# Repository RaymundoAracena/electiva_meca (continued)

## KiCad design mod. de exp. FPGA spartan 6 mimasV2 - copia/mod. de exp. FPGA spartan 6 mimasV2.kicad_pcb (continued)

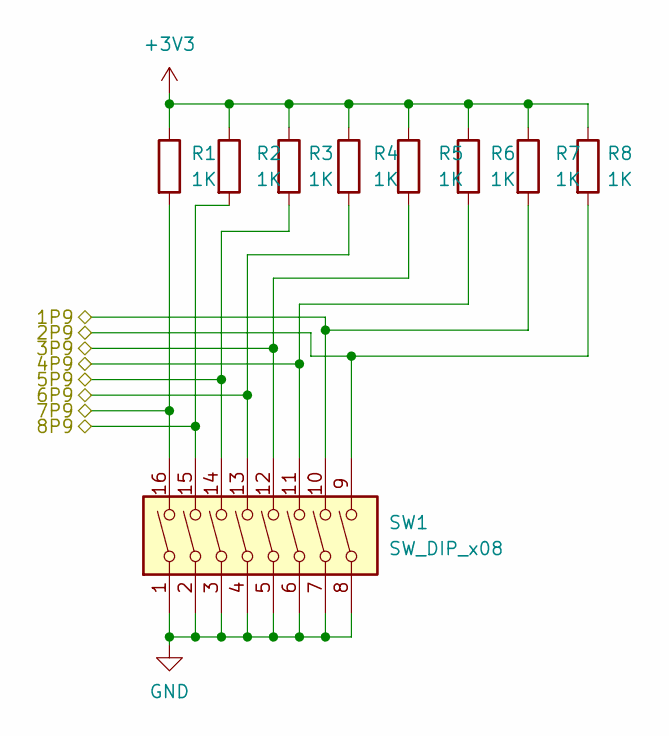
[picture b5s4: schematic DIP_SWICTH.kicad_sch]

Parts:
R1, R2, R3, R4, R5, R6, R7, R8: 1K; R_Axial_DIN0207_L6.3mm_D2.5mm_P10.16mm_Horizontal
SW1: SW_DIP_x08; SW_DIP_SPSTx08_Slide_6.7x21.88mm_W7.62mm_P2.54mm_LowProfile

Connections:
/DIP_SWITCH/1P9: R8.2, SW1.9; also elsewhere on the board
/DIP_SWITCH/2P9: R7.2, SW1.10; also elsewhere on the board
/DIP_SWITCH/3P9: R6.2, SW1.11; also elsewhere on the board
/DIP_SWITCH/4P9: R5.2, SW1.12; also elsewhere on the board
/DIP_SWITCH/5P9: R4.2, SW1.13; also elsewhere on the board
/DIP_SWITCH/6P9: R3.2, SW1.14; also elsewhere on the board
/DIP_SWITCH/7P9: R2.2, SW1.15; also elsewhere on the board
/DIP_SWITCH/8P9: R1.2, SW1.16; also elsewhere on the board

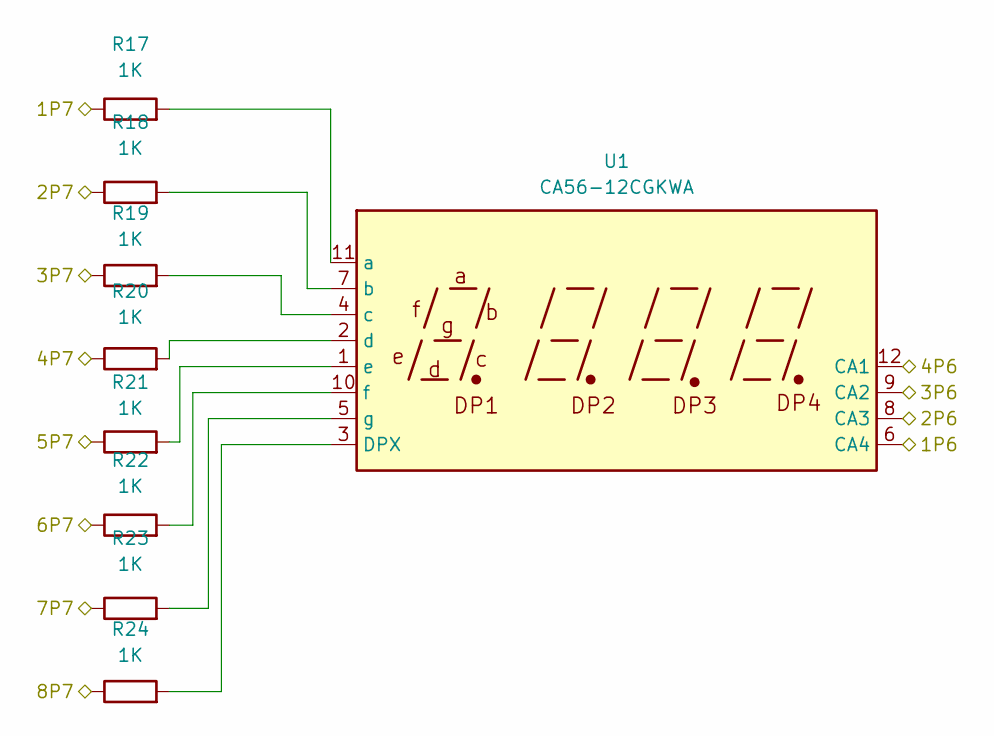
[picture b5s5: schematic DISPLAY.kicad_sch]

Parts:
R17, R18, R19, R20, R21, R22, R23, R24: 1K; R_Axial_DIN0207_L6.3mm_D2.5mm_P7.62mm_Horizontal
U1: CA56-12CGKWA

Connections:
/DISPLAY/1P6: U1.6 (CA4); also elsewhere on the board
/DISPLAY/1P7: R17.1; also elsewhere on the board
/DISPLAY/2P6: U1.8 (CA3); also elsewhere on the board
/DISPLAY/2P7: R18.1; also elsewhere on the board
/DISPLAY/3P6: U1.9 (CA2); also elsewhere on the board
/DISPLAY/3P7: R19.1; also elsewhere on the board
/DISPLAY/4P6: U1.12 (CA1); also elsewhere on the board
/DISPLAY/4P7: R20.1; also elsewhere on the board
/DISPLAY/5P7: R21.1; also elsewhere on the board
/DISPLAY/6P7: R22.1; also elsewhere on the board
/DISPLAY/7P7: R23.1; also elsewhere on the board
/DISPLAY/8P7: R24.1; also elsewhere on the board
unnamed: R24.2, U1.3 (DPX)
unnamed: R17.2, U1.11 (a)
unnamed: R18.2, U1.7 (b)
unnamed: R19.2, U1.4 (c)
unnamed: R20.2, U1.2 (d)
unnamed: R21.2, U1.1 (e)
unnamed: R22.2, U1.10 (f)
unnamed: R23.2, U1.5 (g)

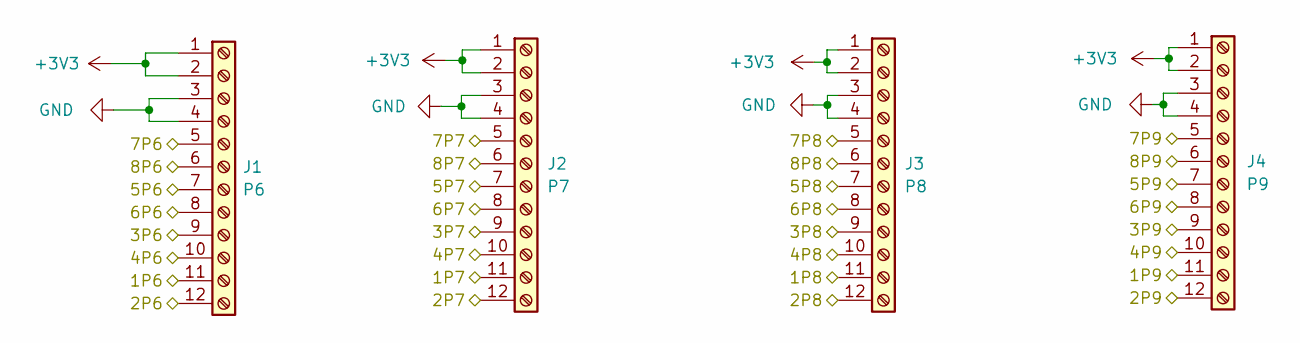
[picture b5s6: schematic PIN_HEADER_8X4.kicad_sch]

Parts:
J1: P6; PinHeader_2x06_P2.54mm_Horizontal
J2: P7; PinHeader_2x06_P2.54mm_Horizontal
J3: P8; PinHeader_2x06_P2.54mm_Horizontal
J4: P9; PinHeader_2x06_P2.54mm_Horizontal

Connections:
/DIP_SWITCH/1P9: J4.11; also elsewhere on the board
/DIP_SWITCH/2P9: J4.12; also elsewhere on the board
/DIP_SWITCH/3P9: J4.9; also elsewhere on the board
/DIP_SWITCH/4P9: J4.10; also elsewhere on the board
/DIP_SWITCH/5P9: J4.7; also elsewhere on the board
/DIP_SWITCH/6P9: J4.8; also elsewhere on the board
/DIP_SWITCH/7P9: J4.5; also elsewhere on the board
/DIP_SWITCH/8P9: J4.6; also elsewhere on the board
/DISPLAY/1P6: J1.11; also elsewhere on the board
/DISPLAY/1P7: J2.11; also elsewhere on the board
/DISPLAY/2P6: J1.12; also elsewhere on the board
/DISPLAY/2P7: J2.12; also elsewhere on the board
/DISPLAY/3P6: J1.9; also elsewhere on the board
/DISPLAY/3P7: J2.9; also elsewhere on the board
/DISPLAY/4P6: J1.10; also elsewhere on the board
/DISPLAY/4P7: J2.10; also elsewhere on the board
/DISPLAY/5P7: J2.7; also elsewhere on the board
/DISPLAY/6P7: J2.8; also elsewhere on the board
/DISPLAY/7P7: J2.5; also elsewhere on the board
/DISPLAY/8P7: J2.6; also elsewhere on the board
/LEDs/1P8: J3.11; also elsewhere on the board
/LEDs/2P8: J3.12; also elsewhere on the board
/LEDs/3P8: J3.9; also elsewhere on the board
/LEDs/4P8: J3.10; also elsewhere on the board
/LEDs/5P8: J3.7; also elsewhere on the board
/LEDs/6P8: J3.8; also elsewhere on the board
/LEDs/7P8: J3.5; also elsewhere on the board
/LEDs/8P8: J3.6; also elsewhere on the board
/PIN_HEADER_8X4/5P6: J1.7; also elsewhere on the board
/PIN_HEADER_8X4/6P6: J1.8; also elsewhere on the board
/PIN_HEADER_8X4/7P6: J1.5; also elsewhere on the board
/PIN_HEADER_8X4/8P6: J1.6; also elsewhere on the board

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
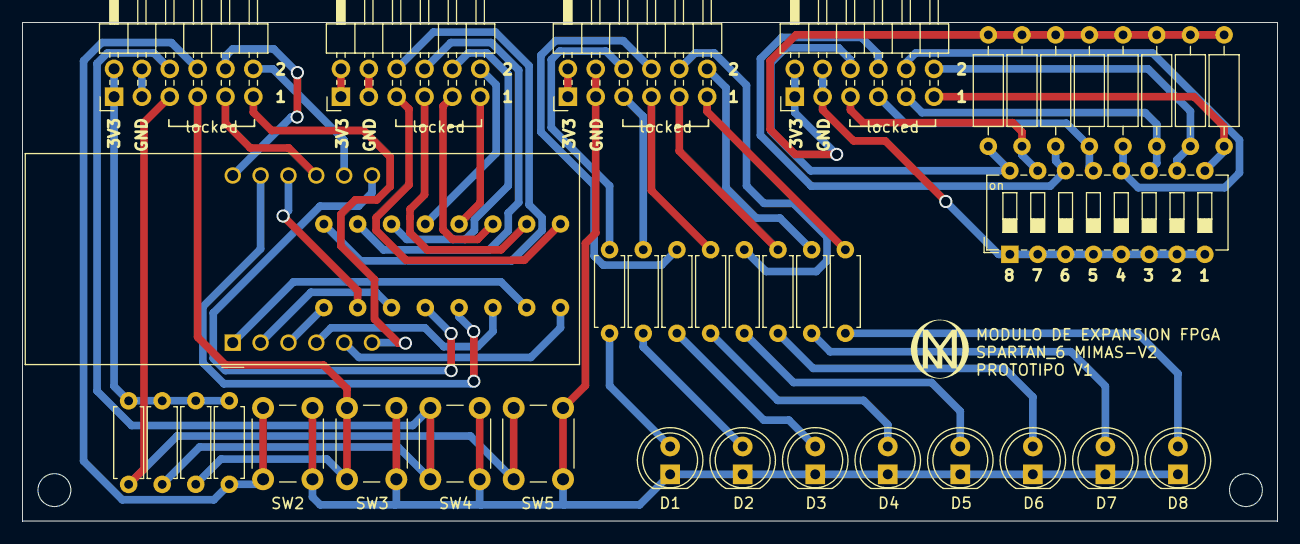
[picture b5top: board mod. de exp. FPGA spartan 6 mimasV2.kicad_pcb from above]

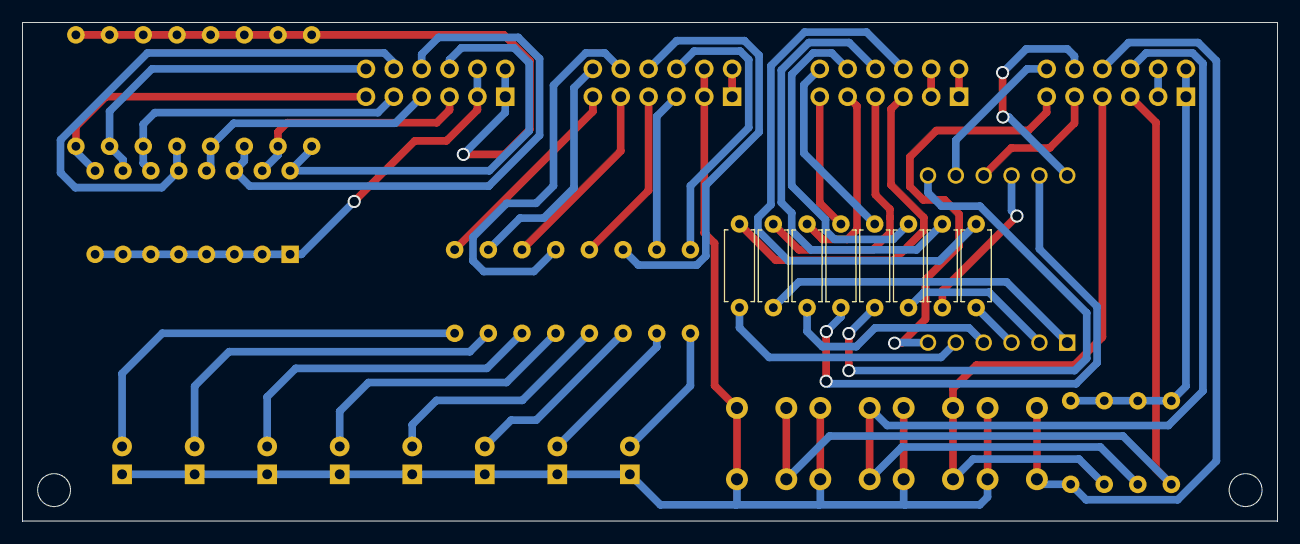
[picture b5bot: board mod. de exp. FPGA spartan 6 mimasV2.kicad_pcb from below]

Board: 2 copper layers, 114.4 x 45.5 mm, 46 parts (8 on the bottom side), 56 nets.

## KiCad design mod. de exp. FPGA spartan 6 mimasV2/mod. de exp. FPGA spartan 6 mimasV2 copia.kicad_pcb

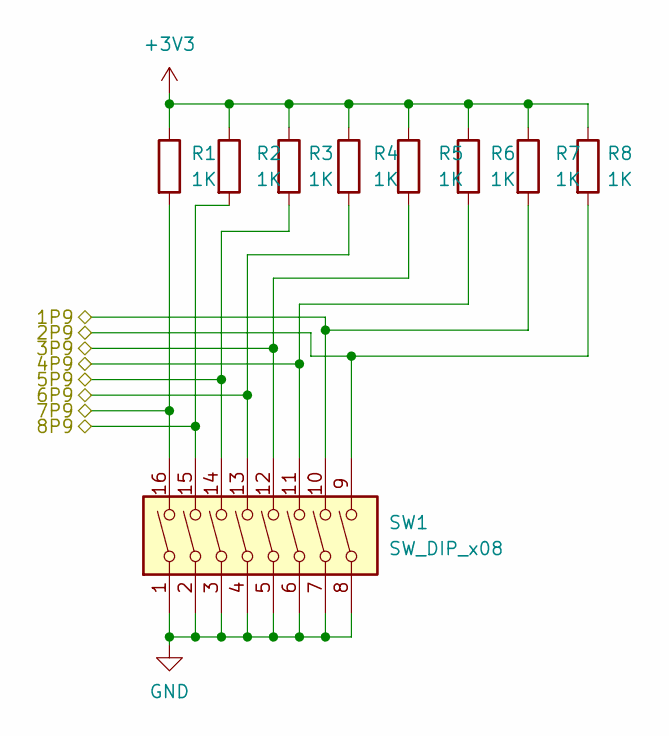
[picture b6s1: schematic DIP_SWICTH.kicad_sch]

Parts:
R1, R2, R3, R4, R5, R6, R7, R8: 1K; R_0805_2012Metric
SW1: SW_DIP_x08; SW_DIP_SPSTx08_Slide_6.7x21.88mm_W7.62mm_P2.54mm_LowProfile

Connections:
+3V3: R1.1, R2.1, R3.1, R4.1, R5.1, R6.1, R7.1, R8.1; also elsewhere on the board
/DIP_SWITCH/1P9: R7.2, SW1.10; also elsewhere on the board
/DIP_SWITCH/2P9: R8.2, SW1.9; also elsewhere on the board
/DIP_SWITCH/3P9: R5.2, SW1.12; also elsewhere on the board
/DIP_SWITCH/4P9: R6.2, SW1.11; also elsewhere on the board
/DIP_SWITCH/5P9: R3.2, SW1.14; also elsewhere on the board
/DIP_SWITCH/6P9: R4.2, SW1.13; also elsewhere on the board
/DIP_SWITCH/7P9: R1.2, SW1.16; also elsewhere on the board
/DIP_SWITCH/8P9: R2.2, SW1.15; also elsewhere on the board
GND: SW1.1, SW1.2, SW1.3, SW1.4, SW1.5, SW1.6, SW1.7, SW1.8; also elsewhere on the board

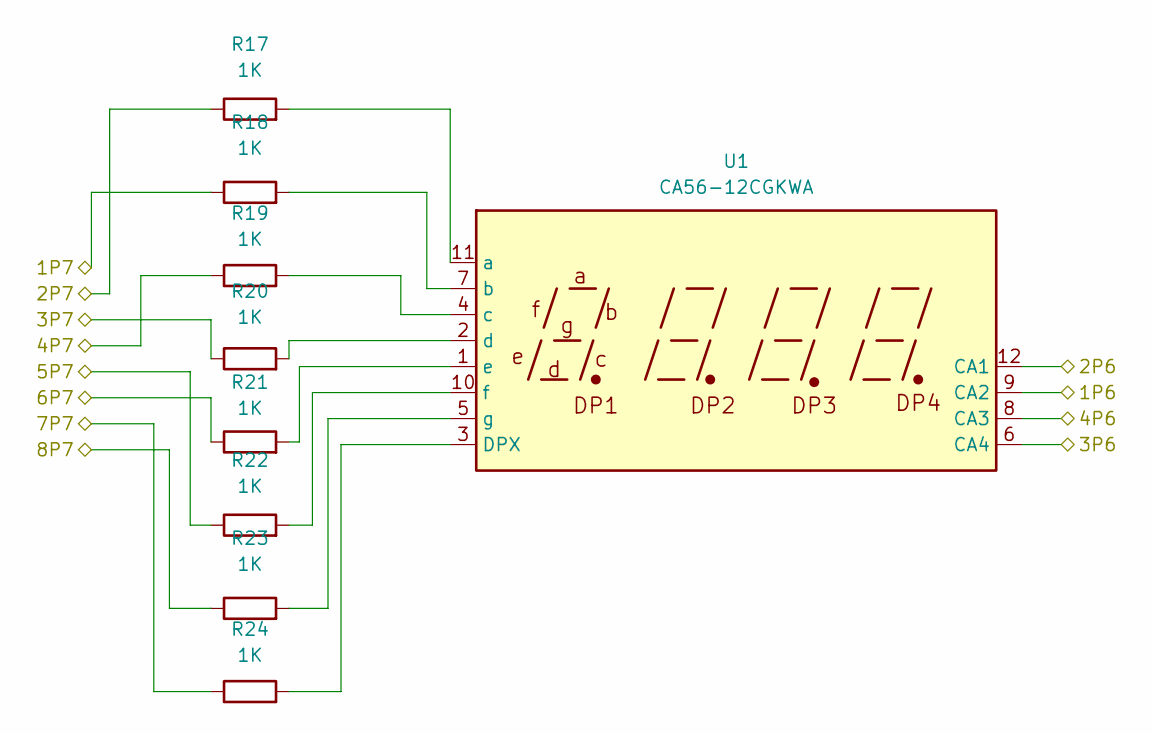
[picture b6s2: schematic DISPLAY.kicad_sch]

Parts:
R17, R18, R19, R20, R21, R22, R23, R24: 1K; R_0805_2012Metric
U1: CA56-12CGKWA

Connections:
/DISPLAY/1P6: U1.9 (CA2); also elsewhere on the board
/DISPLAY/1P7: R18.1; also elsewhere on the board
/DISPLAY/2P6: U1.12 (CA1); also elsewhere on the board
/DISPLAY/2P7: R17.1; also elsewhere on the board
/DISPLAY/3P6: U1.6 (CA4); also elsewhere on the board
/DISPLAY/3P7: R20.1; also elsewhere on the board
/DISPLAY/4P6: U1.8 (CA3); also elsewhere on the board
/DISPLAY/4P7: R19.1; also elsewhere on the board
/DISPLAY/5P7: R22.1; also elsewhere on the board
/DISPLAY/6P7: R21.1; also elsewhere on the board
/DISPLAY/7P7: R24.1; also elsewhere on the board
/DISPLAY/8P7: R23.1; also elsewhere on the board
unnamed: R17.2, U1.11 (a)
unnamed: R18.2, U1.7 (b)
unnamed: R19.2, U1.4 (c)
unnamed: R20.2, U1.2 (d)
unnamed: R21.2, U1.1 (e)
unnamed: R22.2, U1.10 (f)
unnamed: R23.2, U1.5 (g)
unnamed: R24.2, U1.3 (DPX)

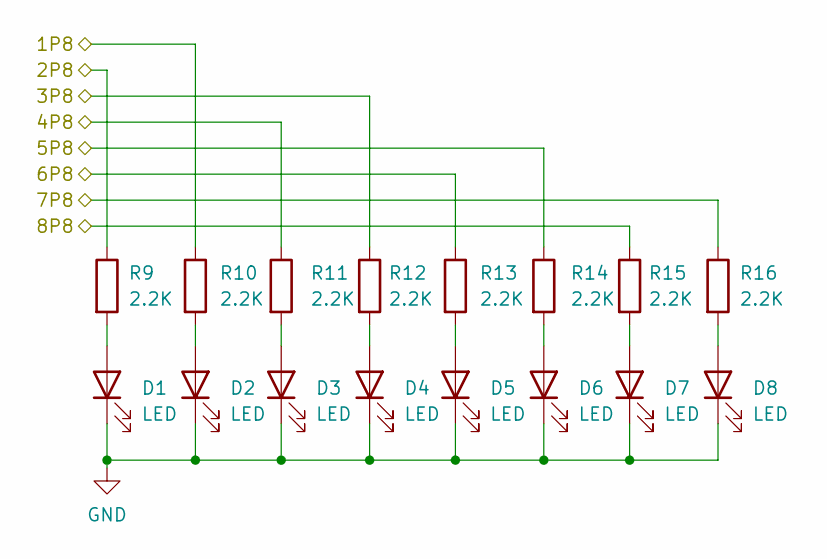
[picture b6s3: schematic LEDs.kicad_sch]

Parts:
D1, D2, D3, D4, D5, D6, D7, D8: LED; LED_0805_2012Metric
R9, R10, R11, R12, R13, R14, R15, R16: 2.2K; R_0805_2012Metric

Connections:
/LEDs/1P8: R10.1; also elsewhere on the board
/LEDs/2P8: R9.1; also elsewhere on the board
/LEDs/3P8: R12.1; also elsewhere on the board
/LEDs/4P8: R11.1; also elsewhere on the board
/LEDs/5P8: R14.1; also elsewhere on the board
/LEDs/6P8: R13.1; also elsewhere on the board
/LEDs/7P8: R16.1; also elsewhere on the board
/LEDs/8P8: R15.1; also elsewhere on the board
GND: D1.1 (K), D2.1 (K), D3.1 (K), D4.1 (K), D5.1 (K), D6.1 (K), D7.1 (K), D8.1 (K); also elsewhere on the board
unnamed: D1.2 (A), R9.2
unnamed: D2.2 (A), R10.2
unnamed: D3.2 (A), R11.2
unnamed: D4.2 (A), R12.2
unnamed: D5.2 (A), R13.2
unnamed: D6.2 (A), R14.2
unnamed: D7.2 (A), R15.2
unnamed: D8.2 (A), R16.2

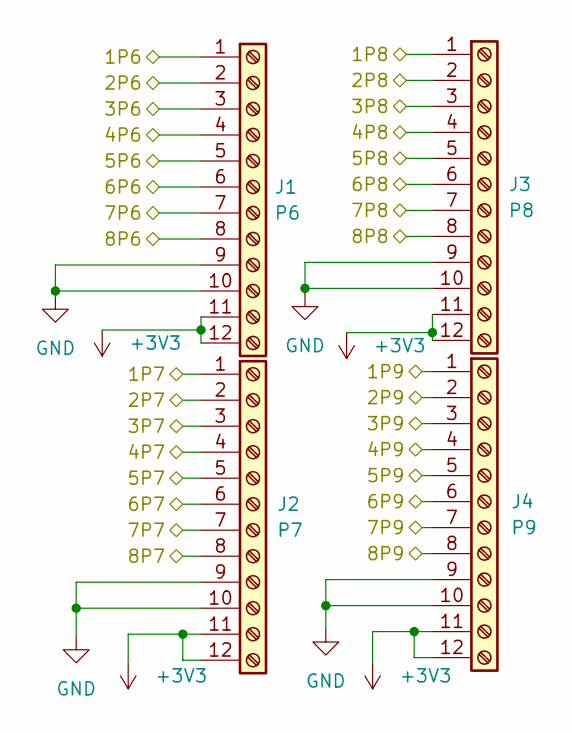
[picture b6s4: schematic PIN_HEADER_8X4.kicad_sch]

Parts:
J1: P6; PinHeader_2x06_P2.54mm_Vertical
J2: P7; PinHeader_2x06_P2.54mm_Vertical
J3: P8; PinHeader_2x06_P2.54mm_Vertical
J4: P9; PinHeader_2x06_P2.54mm_Vertical

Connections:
+3V3: J1.11, J1.12, J2.11, J2.12, J3.11, J3.12, J4.11, J4.12; also elsewhere on the board
/DIP_SWITCH/1P9: J4.1; also elsewhere on the board
/DIP_SWITCH/2P9: J4.2; also elsewhere on the board
/DIP_SWITCH/3P9: J4.3; also elsewhere on the board
/DIP_SWITCH/4P9: J4.4; also elsewhere on the board
/DIP_SWITCH/5P9: J4.5; also elsewhere on the board
/DIP_SWITCH/6P9: J4.6; also elsewhere on the board
/DIP_SWITCH/7P9: J4.7; also elsewhere on the board
/DIP_SWITCH/8P9: J4.8; also elsewhere on the board
/DISPLAY/1P6: J1.1; also elsewhere on the board
/DISPLAY/1P7: J2.1; also elsewhere on the board
/DISPLAY/2P6: J1.2; also elsewhere on the board
/DISPLAY/2P7: J2.2; also elsewhere on the board
/DISPLAY/3P6: J1.3; also elsewhere on the board
/DISPLAY/3P7: J2.3; also elsewhere on the board
/DISPLAY/4P6: J1.4; also elsewhere on the board
/DISPLAY/4P7: J2.4; also elsewhere on the board
/DISPLAY/5P7: J2.5; also elsewhere on the board
/DISPLAY/6P7: J2.6; also elsewhere on the board
/DISPLAY/7P7: J2.7; also elsewhere on the board
/DISPLAY/8P7: J2.8; also elsewhere on the board
/LEDs/1P8: J3.1; also elsewhere on the board
/LEDs/2P8: J3.2; also elsewhere on the board
/LEDs/3P8: J3.3; also elsewhere on the board
/LEDs/4P8: J3.4; also elsewhere on the board
/LEDs/5P8: J3.5; also elsewhere on the board
/LEDs/6P8: J3.6; also elsewhere on the board
/LEDs/7P8: J3.7; also elsewhere on the board
/LEDs/8P8: J3.8; also elsewhere on the board
/PIN_HEADER_8X4/5P6: J1.5; also elsewhere on the board
/PIN_HEADER_8X4/6P6: J1.6; also elsewhere on the board
/PIN_HEADER_8X4/7P6: J1.7; also elsewhere on the board
/PIN_HEADER_8X4/8P6: J1.8; also elsewhere on the board
GND: J1.9, J1.10, J2.9, J2.10, J3.9, J3.10, J4.9, J4.10; also elsewhere on the board

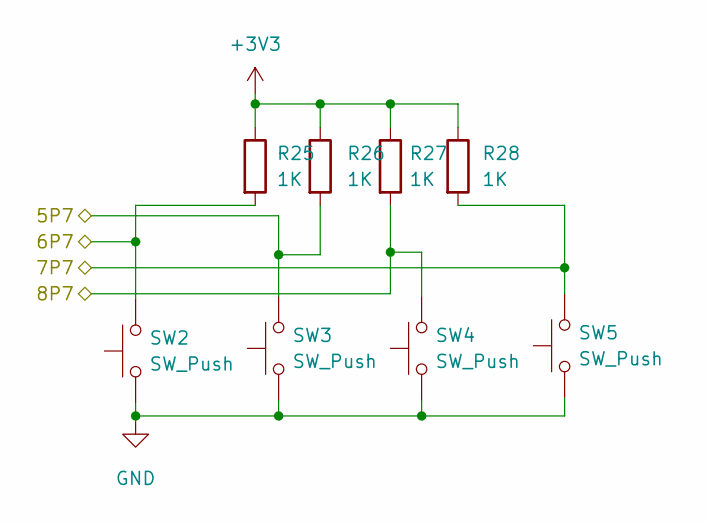
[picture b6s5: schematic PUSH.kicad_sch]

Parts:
R25, R26, R27, R28: 1K; R_0805_2012Metric
SW2, SW3, SW4, SW5: SW_Push; SW_PUSH_6mm

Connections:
+3V3: R25.1, R26.1, R27.1, R28.1; also elsewhere on the board
/PIN_HEADER_8X4/5P6: R26.2, SW3.2; also elsewhere on the board
/PIN_HEADER_8X4/6P6: R25.2, SW2.2; also elsewhere on the board
/PIN_HEADER_8X4/7P6: R28.2, SW5.2; also elsewhere on the board
/PIN_HEADER_8X4/8P6: R27.2, SW4.2; also elsewhere on the board
GND: SW2.1, SW3.1, SW4.1, SW5.1; also elsewhere on the board

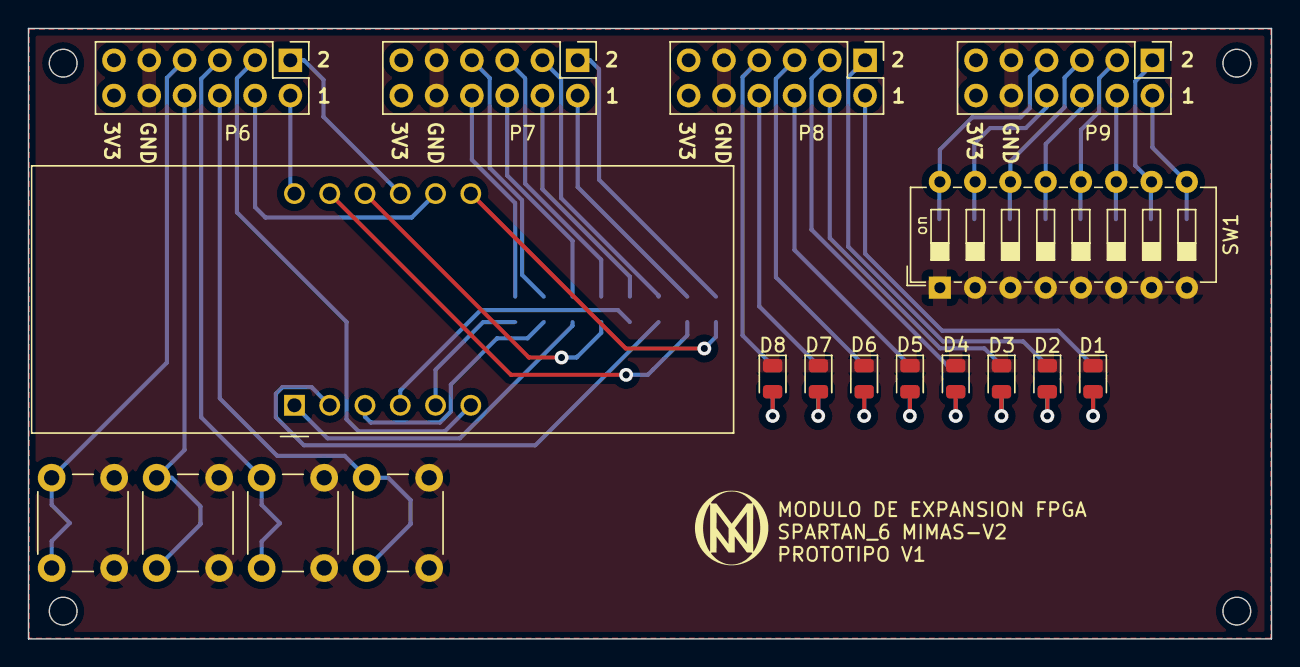
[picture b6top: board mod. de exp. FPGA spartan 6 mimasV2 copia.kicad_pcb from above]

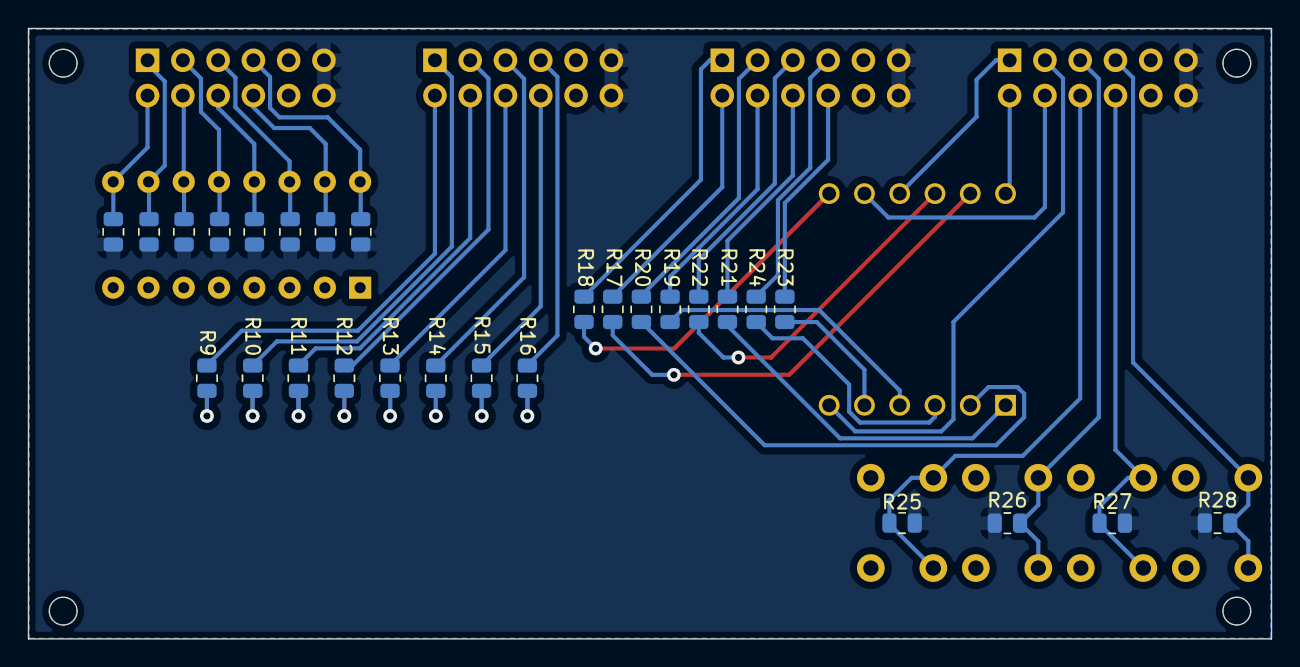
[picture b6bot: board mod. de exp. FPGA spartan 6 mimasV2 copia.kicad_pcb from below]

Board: 2 copper layers, 89.5 x 44.0 mm, 46 parts (28 on the bottom side), 50 nets.

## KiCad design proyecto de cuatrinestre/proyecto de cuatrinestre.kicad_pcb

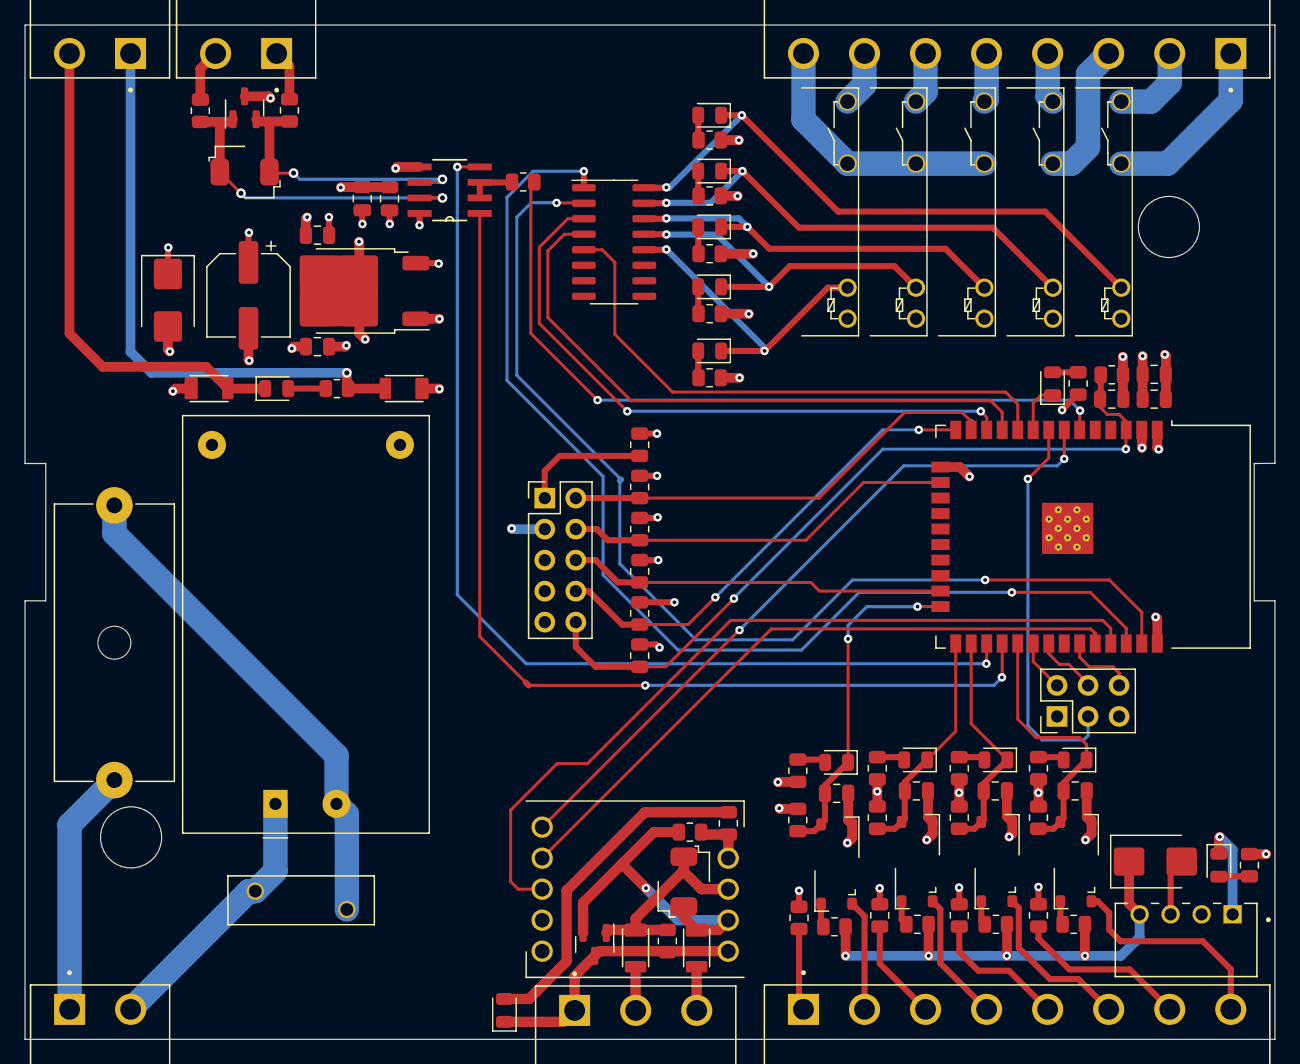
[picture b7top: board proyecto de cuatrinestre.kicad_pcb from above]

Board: 4 copper layers, 102.4 x 83.1 mm, 98 parts (0 on the bottom side), 85 nets.

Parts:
C1, C2, C3, C4, C5, C13: 0.1uF; C_0805_2012Metric
C7, C9, C10: 0.1uF / 25V; C_0805_2012Metric
C8: 0.1uF / 50V; C_0805_2012Metric
C11: 47uF; CP_Elec_6.3x5.7
C12: 22uF; C_0805_2012Metric
D1, D2, D3, D4, D5, D6, D7, D8, D9, D10, D12, D14, D16: LED; LED_0805_2012Metric
D11, D13: SM712_SOT23; SOT-23
D17, D18: 1SMA5918BT3G; D_SMB
F1, F2: PTS120660V010; RESC3115X65N
F3: Fuse; Fuseholder_Cylinder-5x20mm_Schurter_0031_8201_Horizontal_Op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
F4, F5: Fuse; RESC3115X65N
J1, J2, J3: Screw_Terminal_01x02; CUI_TBP04R12-500-02GR
J4: Screw_Terminal_01x03; CUI_TBP04R12-500-03GR
J5, J6: Screw_Terminal_01x08; CUI_TBP04R12-500-08GR
J7: Screw_Terminal_01x06; PinHeader_2x03_P2.54mm_Vertical
J8: ESP32-JTAG; PinHeader_2x05_P2.54mm_Vertical
PS1: HLK-PM12; Converter_ACDC_HiLink_HLK-PMxx
R1, R3, R9, R11: 330; R_0805_2012Metric
R2, R4, R10, R12, R43, R44: 10; R_0805_2012Metric
R5, R6, R13, R14: 10k; R_0805_2012Metric
R7, R8, R15, R16, R39: 470; R_0805_2012Metric
R17, R18, R19, R20, R21: 1K; R_0805_2012Metric
R22: 2.2k; R_0805_2012Metric
R23, R24: 2.2; R_0805_2012Metric
R27, R33: 22K; R_0805_2012Metric
R28, R29, R30, R31, R32: 10K; R_0805_2012Metric
R42: 10 / 1%; R_0805_2012Metric
R45, R47: R; R_0805_2012Metric
RV1: V10E275P; VAR_B72210S1140K501
U1: TD521D485H-E
U2, U3, U4, U5: FODM2705
U6: ULN2003A; SOIC-16_3.9x9.9mm_P1.27mm
U7, U8, U9, U10, U11: AZ921
U12, U14: SMBJ12CA
U13: SP485ECN-L; SOIC127P600X175-8N
U15: 3v3 NJM2885DL1-33; TO-252-2
U16: B0303S-W2R2; CONV_B0505S-1WR2
U17: ESP32-WROOM-32

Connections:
+3V3: D18.1, R1.1, R3.1, R9.1, R11.1, U16.4 (OUT+)
+12V: C9.1, F4.1, PS1.4 (+Vout), R17.2, R18.2, R19.2, R20.2, R21.2, U7.1, U8.1, U9.1, U10.1, U11.1, U15.1 (Vin)
/ROOMLINK/CON-A-: F2.2, J4.3
/ROOMLINK/CON-B+: F1.2, J4.2
/ROOMLINK/CON-DC+: F4.2, J2.1, R45.1
/ROOMLINK/CON-DC-: D14.1 (K), F5.2, J2.2
/ROOMLINK/CON-FAN1: J5.7, U9.4
/ROOMLINK/CON-FAN2: J5.6, U10.4
/ROOMLINK/CON-FAN3: J5.5, U11.4
/ROOMLINK/CON-FAN-C: J5.8, U9.3, U10.3, U11.3
/ROOMLINK/CON-IN1+: J6.8, U2.2
/ROOMLINK/CON-IN1-: J6.7, R2.2
/ROOMLINK/CON-IN2+: J6.6, U3.2
/ROOMLINK/CON-IN2-: J6.5, R4.2
/ROOMLINK/CON-IN3+: J6.4, U5.2
/ROOMLINK/CON-IN3-: J6.3, R12.2
/ROOMLINK/CON-IN4+: J6.2, U4.2
/ROOMLINK/CON-IN4-: J6.1, R10.2
/ROOMLINK/CON-L1: F3.2, J1.1
/ROOMLINK/CON-LCDA-: J3.1, R43.2
/ROOMLINK/CON-LCDB+: J3.2, R44.2
/ROOMLINK/CON-NEUT: J1.2, PS1.1 (AC/L), RV1.1
/ROOMLINK/CON-OUT1A: J5.3, U7.3
/ROOMLINK/CON-OUT1B: J5.4, U7.4
/ROOMLINK/CON-OUT2A: J5.1, U8.3
/ROOMLINK/CON-OUT2B: J5.2, U8.4
/ROOMLINK/CONTROL/COM_RS485_LCD: R42.1, U17.6 (IO34)
/ROOMLINK/CONTROL/CON_RS485_eXT: U1.5 (CON), U17.7 (IO35)
/ROOMLINK/CONTROL/INPUT_1_MICRO: C1.1, D1.1 (K), R5.2, U2.4, U17.29 (IO5)
/ROOMLINK/CONTROL/INPUT_2_MICRO: C2.1, D2.1 (K), R6.2, U3.4, U17.26 (IO4)
/ROOMLINK/CONTROL/INPUT_3_MICRO: C4.1, D4.1 (K), R14.2, U5.4, U17.25 (IO0)
/ROOMLINK/CONTROL/INPUT_4_MICRO: C3.1, D3.1 (K), R13.2, U4.4, U17.24 (IO2)
/ROOMLINK/CONTROL/RLY_FAN1_MICRO: U6.5 (I5), U17.10 (IO25)
/ROOMLINK/CONTROL/RLY_FAN2_MICRO: U6.4 (I4), U17.11 (IO26)
/ROOMLINK/CONTROL/RLY_FAN3_MICRO: U6.3 (I3), U17.12 (IO27)
/ROOMLINK/CONTROL/RLY_OUT1_MICRO: U6.1 (I1), U17.36 (IO22)
/ROOMLINK/CONTROL/RLY_OUT2_MICRO: U6.2 (I2), U17.37 (IO23)
/ROOMLINK/CONTROL/Rx_RS485_eXT: U1.4 (RXD), U17.34 (RXD0/IO3)
/ROOMLINK/CONTROL/Rx_RS485_lcd: U13.4 (DI), U17.27 (IO16)
/ROOMLINK/CONTROL/Tx_RS485_LCD: U13.1 (RO), U17.28 (IO17)
/ROOMLINK/CONTROL/Tx_RS485_eXT: U1.3 (TXD), U17.35 (TXD0/IO1)
/ROOMLINK/RGND: D10.1 (K), D11.3 (common), J4.1, R23.1, U1.10 (RGND)
GND: C1.2, C2.2, C3.2, C4.2, C7.2, C8.2, C9.2, C10.2, C11.2, C12.2, C13.2, D13.3 (common), D16.1 (K), D17.2, F5.1, J7.5, J8.3 (GND), J8.9 (GNDDetect), PS1.3 (-Vout), U1.2 (GND), U2.3, U3.3, U4.3, U5.3, U13.5 (GND), U15.2 (GND), U16.1 (IN-), U17.1 (GND), U17.15 (GND), U17.38 (GND), U17.39 (GND)
GNDA: D18.2, R2.1, R4.1, R10.1, R12.1, U16.3 (OUT-)
unnamed: D1.2 (A), R7.2
unnamed: D2.2 (A), R8.2
unnamed: D3.2 (A), R15.2
unnamed: D4.2 (A), R16.2
unnamed: D5.2 (A), R17.1
unnamed: D5.1 (K), U6.16 (O1), U8.2
unnamed: D6.2 (A), R18.1
unnamed: D6.1 (K), U6.15 (O2), U7.2
unnamed: D7.2 (A), R19.1
unnamed: D7.1 (K), U6.14 (O3), U11.2
unnamed: D8.2 (A), R20.1
unnamed: D8.1 (K), U6.13 (O4), U10.2
unnamed: D9.2 (A), R21.1
unnamed: D9.1 (K), U6.12 (O5), U9.2
unnamed: D10.2 (A), R24.2
unnamed: D11.1 (A1), F1.1, R23.2, U1.8 (B), U12.1
unnamed: D11.2 (A2), F2.1, R22.2, U1.9 (A), U12.2
unnamed: D12.2 (A), R39.1
unnamed: D12.1 (K), U17.9 (IO33)
unnamed: D13.1 (A1), R44.1, U13.7 (B), U14.1
unnamed: D13.2 (A2), R43.1, U13.6 (A), U14.2
unnamed: D14.2 (A), R45.2
unnamed: D16.2 (A), R47.2
unnamed: J7.2, U17.30 (IO18)
unnamed: J7.3, U17.8 (IO32)
unnamed: J7.4, U17.31 (IO19)
unnamed: J7.6, U17.33 (IO21)
unnamed: J8.1 (VTRef), R27.1
unnamed: F3.1, PS1.2 (AC/N), RV1.2
unnamed: R1.2, U2.1
unnamed: R3.2, U3.1
unnamed: R9.2, U4.1
unnamed: R11.2, U5.1
unnamed: R22.1, R24.1, U1.7 (Vo)
unnamed: R42.2, U13.2 (~RE), U13.3 (DE)
TCK: J8.4 (TCK), R29.1, U17.16 (IO13)
TDI: J8.8 (TDI), R31.1, U17.14 (IO12)
TDO: J8.6 (TDO), R30.1, U17.23 (IO15)
TMS: J8.2 (TMS), R28.1, U17.13 (IO14)
VDD: C5.1, C7.1, C8.1, C10.1, C11.1, C12.1, C13.1, D17.1, J7.1, R5.1, R6.1, R7.1, R8.1, R13.1, R14.1, R15.1, R16.1, R27.2, R28.2, R29.2, R30.2, R31.2, R32.2, R33.2, R39.2, R47.1, U1.1 (Vcc), U13.8 (VCC), U15.3 (Vout), U16.2 (IN+), U17.2 (VDD)
nRESET: C5.2, J8.10 (nRESET), R32.1, R33.1, U17.3 (EN)
